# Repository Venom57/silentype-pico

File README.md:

# silentype-pico

USB controller for the **Apple Silentype** thermal printer (1980, Trendcom 200 mechanism),
built on a Raspberry Pi Pico 2, with a host-side PAPPL printer application that presents it
to macOS and Linux as an IPP Everywhere printer (no driver install). The printer itself is not
modified: the carrier board plugs into its original DE-9 cable.

## Why this works

The Silentype has no processor. Apple used the Trendcom mechanism without Trendcom's
controller, so the host does all the timing; on the Apple II that host was the interface
card's 2 KB ROM running on the 6502. Inside the printer there is only a 74LS673 16-bit shift
register with an output latch, three ULN2003 driver arrays (7-dot head, carriage stepper,
paper stepper), a 555 head-on watchdog and a margin switch. Anything that produces the right
16-bit words at the right times can drive it. The Pico replaces the card and the 6502.

## Architecture

The host turns pages into 7-dot bands; the Pico turns bands into exactly timed 16-bit words; the
carrier converts levels and fails safe; the printer, unchanged, latches and drives. Details in the
[design overview](docs/design-overview.md).

## Documentation

| Document | What it covers |
|---|---|
| [Design overview](docs/design-overview.md) | Architecture, design principles, design-decision log, glossary |
| [Printer interface](docs/printer-interface.md) | Sources, printer electronics, DE-9 pinout, the 16-bit word, bus timing diagram, Apple's card decode, print timing tables, motion, corrections log |
| [Firmware design](docs/firmware-design.md) | Execution model, PIO transport, column schedule, motion, queue and errors, safety, configuration and SET_PARAM, tests, open issues |
| [Host software](docs/host-software.md) | USB transport, ACK flow control, PAPPL app, `send_band.py`, installation, open issues |
| [Band protocol](docs/protocol.md) | Wire format: frames, commands, payloads, example bytes |
| [Carrier board](hardware/pcb/README.md) | Build pipeline, circuit, schematic sheets, renders, layout rules |
| [Bill of materials](hardware/BOM.md) | Component choices; [`BOM.csv`](hardware/BOM.csv) generated from the board |
| [Bring-up and tests](docs/bring-up.md) | What is verified, bench procedure with pass criteria, milestone plan, measurement log |
| [Known issues](docs/KNOWN-ISSUES.md) | Audit trail and every open issue |
| [Hardware interface evidence](docs/firmware-archaeology/HARDWARE-INTERFACE.md) | Signal-by-signal evidence from Apple's schematics and ROM |
| [Firmware README](firmware/README.md) | Build, file map, pins |

## Gallery

| Bare PCB, front | Bare PCB, back (mirrored) |
|---|---|
|  |  |

| Printer bus schematic | Bus timing |
|---|---|
|  |  |

| Firmware execution model | Host ACK flow |
|---|---|
|  |  |

More: [power and input schematics](hardware/pcb/README.md#schematic), [assembled top view](docs/images/render-top.png).

## Repository map

| Path | Contents |
|---|---|
| `firmware/` | Pico SDK project: CMake, TinyUSB CDC, PIO transport, print engine |
| `firmware/test/` | Host-side test harness: runs the real engine and parser on a PC (`make -C firmware/test`) |
| `hardware/pcb/` | Carrier v1.0 generated from code: `build_carrier.py`, `Makefile`, KiCad board, Gerbers, renders |
| `hardware/BOM.csv`, `hardware/BOM.md` | Bill of materials and component notes for carrier v1.0 |
| `host/pappl-app/` | PAPPL printer application |
| `host/tools/send_band.py` | Bench tool (no CUPS needed) |
| `host/linux/`, `host/macos/` | udev rule, systemd unit, launchd agent |
| `docs/protocol.md` | Band protocol (host ⇄ Pico) |
| `docs/signals.md` | DE-9 signal map and bus waveform |
| `docs/*.md` | Design documents (see Documentation above); `docs/images/` holds renders and diagrams |
| `docs/bring-up.md` | Bench bring-up procedure, milestone test plan, measurement log |
| `docs/KNOWN-ISSUES.md` | Audit trail and open issues |
| `docs/firmware-archaeology/` | Apple /// driver, Apple II card ROM, schematics, `HARDWARE-INTERFACE.md` (the definitive interface) |
| `docs/reference/` | Silentype manual, TA27850 pinout, Trendcom manual |

## Quick start

```
# firmware (needs the Pico SDK and an ARM toolchain)
export PICO_SDK_PATH=~/pico-sdk
cmake -B build -S firmware && cmake --build build      # → build/silentype.uf2

# firmware tests on the PC (gcc only)
make -C firmware/test

# printer-app tests against a fake Pico (needs PAPPL headers)
make -C host/pappl-app test

# carrier PCB: regenerate, route, DRC, Gerbers, renders (KiCad 10, Java 25, Freerouting 2.5)
make -C hardware/pcb FREEROUTING_JAR=/path/to/freerouting-2.5.0.jar

# talk to the printer without CUPS
python3 host/tools/send_band.py status
```

The PCB fab package is `hardware/pcb/fab/silentype-carrier-gerbers.zip` (2 layers, 1.6 mm,
100 × 56 mm; standard JLCPCB/PCBWay rules).

## Status

| Area | State |
|---|---|
| Reverse engineering | Done: Apple /// driver, Apple II card ROM, printer and card schematics, DE-9 pinout |
| Firmware | Written; host-simulated tests pass; **not yet built with the real Pico SDK** |
| Carrier PCB v1.0 | Routed, DRC clean (0 errors, 0 unconnected), Gerbers exported; not yet ordered |
| PAPPL app | Builds against libpappl 1.4.12 with no warnings; fake-Pico test passes (`make -C host/pappl-app test`); a real PAPPL server added the printer and printed a PNG end to end to a fake Pico. Not yet tried from a desktop print dialog or with a real printer |
| Bench | Not started |

## Milestones

- [x] **M0a** Apple /// SOS driver found and disassembled
- [x] **M0b** Card ROM, both schematics and DE-9 pinout found; serial PIO transport written
- [ ] **M1** Bench characterisation: head element count and resistance, supply current
- [ ] **M2** Carrier built; margin switch readable; bus enable and store verified on the scope
- [ ] **M3** Carriage homes and sweeps under Pico control
- [ ] **M4** A single column burns cleanly at conservative timing
- [ ] **M5** Test-pattern band prints in both directions
- [ ] **M6** Band protocol end to end via `host/tools/send_band.py`
- [ ] **M7** PAPPL app prints PWG raster; visible in the macOS/Linux print dialog
- [ ] **M8** `lp -d silentype file.pdf` produces paper
- [ ] **M9** Reverse-pass registration tuned

Pass criteria for each are in `docs/bring-up.md`.

## Safety model (read before powering anything)

The print head is the one irreplaceable part. Three independent layers turn it off:

1. **Printer's 555 watchdog (inside the printer).** It watches the head driver outputs; if any
   element stays on for about 5–6 ms it clears the 74LS673's outputs, motors included.
2. **Carrier bus enable (hardware).** The 74AHCT541 drives the bus only while GP6 is high. When
   the Pico is in reset, unpowered, or the guard drops GP6, the buffer releases the bus and the
   carrier's pull-ups hold SC = XC = 1, which asynchronously clears every printer output.
3. **Software guard (firmware).** Every burn is capped at 3000 µs, and an alarm on core 0 drops
   GP6 if a burn overruns. This catches logic bugs; it is not a substitute for 1 and 2.

Plus: fused 12 V (2 A PTC, reverse-polarity crowbar), fused printer 5 V (0.5 A PTC), and a
current-limited bench supply for first power-up. The firmware defaults to intensity level 1,
well below Apple's default 5, until the head has been characterised.

## Ground truth

All timing and bit positions come from Apple's own code and schematics, archived in
`docs/firmware-archaeology/`: the Apple /// `.SILENTYPE` driver (7-element head, burn timing,
wave-drive stepping, bidirectional printing with 2-column thermal lookback), the Apple II card
ROM 341-0039-00 with Marc Ressl's disassembly (exact bit order, store sequence, 8-level burn
table), the printer schematic 050-0023-01, the card schematics 050-0024-00/-01 and Apple KB
TA27850. `HARDWARE-INTERFACE.md` is the definitive summary.

Still unknown until the bench: exact column count on paper, reverse-pass trim, head element
resistance, and which of Apple's two burn tables the head prefers.

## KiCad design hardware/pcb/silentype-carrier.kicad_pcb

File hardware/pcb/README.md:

# Carrier board v1.0

[README](../../README.md) · [Design overview](../../docs/design-overview.md) · [Printer interface](../../docs/printer-interface.md) · [Firmware design](../../docs/firmware-design.md) · [Host software](../../docs/host-software.md) · **Carrier board** · [Bring-up and tests](../../docs/bring-up.md)

100 × 56 mm, 2-layer, all through-hole. Routed, **DRC clean (0 errors, 0 unconnected)**,
Gerbers exported; not yet ordered. The whole board is generated from `build_carrier.py`.

| File | What it is |
|---|---|
| `build_carrier.py` | Parts, nets, placement, design rules, keepouts, silkscreen; `place`, `finish`, `bare` steps |
| `gen_resistor_models.py` | Writes `models/`: resistor models with the correct 4-band colour code, and Bourns MF-RHT PTC fuse models |
| `check_drc.py` | Fails the build on any DRC error or unconnected net |
| `Makefile` | The whole pipeline |
| `silentype-carrier.kicad_pcb` | The generated, routed board (open it in KiCad 10 to inspect) |
| `fab/` | Outputs: `silentype-carrier-gerbers.zip`, drill files and maps, placement CSV, DRC report, renders |

## Build

```
make FREEROUTING_JAR=/path/to/freerouting-2.5.0.jar     # default: ~/.local/share/freerouting/
```

Needs KiCad 10 (`kicad-cli` and its Python `pcbnew` module), Java 25 and the Freerouting 2.5
jar (the linux-arm64 native CLI crashes after its first pass). Steps:

1. `gen_resistor_models.py` writes the banded resistor models.
2. `build_carrier.py place` builds the board and exports a Specctra DSN (silkscreen outlines and
   the GND net are removed from the DSN: GND is poured, not routed).
3. Freerouting routes every other net.
4. `build_carrier.py finish` imports the routes, pours GND on both layers, lays out silkscreen.
5. KiCad DRC; `check_drc.py` stops the build on any error or unconnected net.
6. `fab`: Gerbers (F/B copper, mask, paste, silk, edge), Excellon PTH/NPTH, drill maps, zip.
7. `render`: assembled top, bottom and angled views, plus bare-board front and back.

`make models` fetches only the 3D models this board uses from KiCad's official library into
`~/.local/share/kicad/3dmodels` (no system install needed). Renders only; Gerbers never depend on
3D models.

## Circuit

| Block | Parts | Function |
|---|---|---|
| Printer connector | J1 DE-9 female | Apple KB TA27850 pinout: 2 +5 V, 3/7 GND, 4 SD, 5 MS, 6 +12 V, 8 XC, 9 SC |
| 12 V input | J2, F1 2 A PTC, D1 1N5822, C1 470 µF | Head and motor supply; D1 crowbars a reversed plug so F1 trips |
| 5 V | U3 R-78E5.0-1.0, C2, C3, F2 0.5 A PTC → +5V_PRN; D2 → VSYS | Printer logic, buffer, Pico |
| Bus buffer | U2 74AHCT541, R1–R3 47 Ω | SD/SC/XC from 3.3 V to 5 V TTL (channels A2/A3/A1; spare inputs grounded) |
| Fail-safe enable | Q1 2N3904, R7 10 k (OE̅ pull-up), R8 4.7 k, R9 47 k, R4/R5 4.7 k pull-ups, R6 10 k pull-down | GP6 high → U2 drives. GP6 low, Pico in reset or unpowered → bus released, SC = XC = 1, printer cleared |
| Margin switch | R10 1 k, R11 10 k to 3V3, D3 BAT85 | MS → GP5, clamped to 3.3 V |
| Interface | SW1 feed (GP22), LED1 error (GP26, R12), LED2 power (R13), J3 UART (GP0/GP1) | Bench use |
| Test points | TP1 SD, TP2 SC, TP3 XC, TP4 MS, TP5 +12 V, TP6 +5 V, TP7 GND | Scope access |

## Schematic

Drawn from the generator's net list; `build_carrier.py` is authoritative.

## Renders

| Bare PCB, front | Bare PCB, back (mirrored) |
|---|---|
|  |  |

Resistors carry their real 4-band codes (models from `gen_resistor_models.py`); F1 and F2 are
yellow PTC polyfuses, labelled "F1 PTC 2A" and "F2 PTC 0.5A" on the silkscreen; each electrolytic
has a bold "+" beside its positive pad; diodes are marked "K" at the cathode.

## Layout and rules

- Cables enter on the left edge (jack top, DE-9 below). The Pico 2 / 2 W sits on 8.5 mm sockets
  along the right edge, USB at the top edge; its antenna end reaches the bottom edge with a
  no-copper keepout on both layers.
- Tracks 0.3 mm / clearance 0.2 mm; +12 V 1.2 mm; +5 V and GND 0.6 mm; vias 0.7/0.35 mm. Minimum
  track 0.15 mm because the router necks to about 0.18 mm between header pins (fab minimum 0.127).
- GND poured on both layers; Pico GND pins connect solid (edge pins cannot fit two spokes).
- Silkscreen: reference designators inside axial bodies; "F1 PTC 2A" / "F2 PTC 0.5A" fuse labels; bold "+" beside each electrolytic's
  positive pad; "K" at diode cathodes; UART pin labels; board title on the back between the
  Pico's pin rows.

## Render notes

KiCad's library has no 3D models for the CUI PJ-102AH jack (KiCad's generic jack stands in) or
the Bourns MF-RHT PTC fuses (generated by `gen_resistor_models.py`: yellow epoxy body on two legs). KiCad 10.0.7 on aarch64 crashes loading most `CP_Radial`/`C_Radial` STEP
models; the D10 dual-pitch can loads, so it is used for C1 and, scaled, for C2/C3.

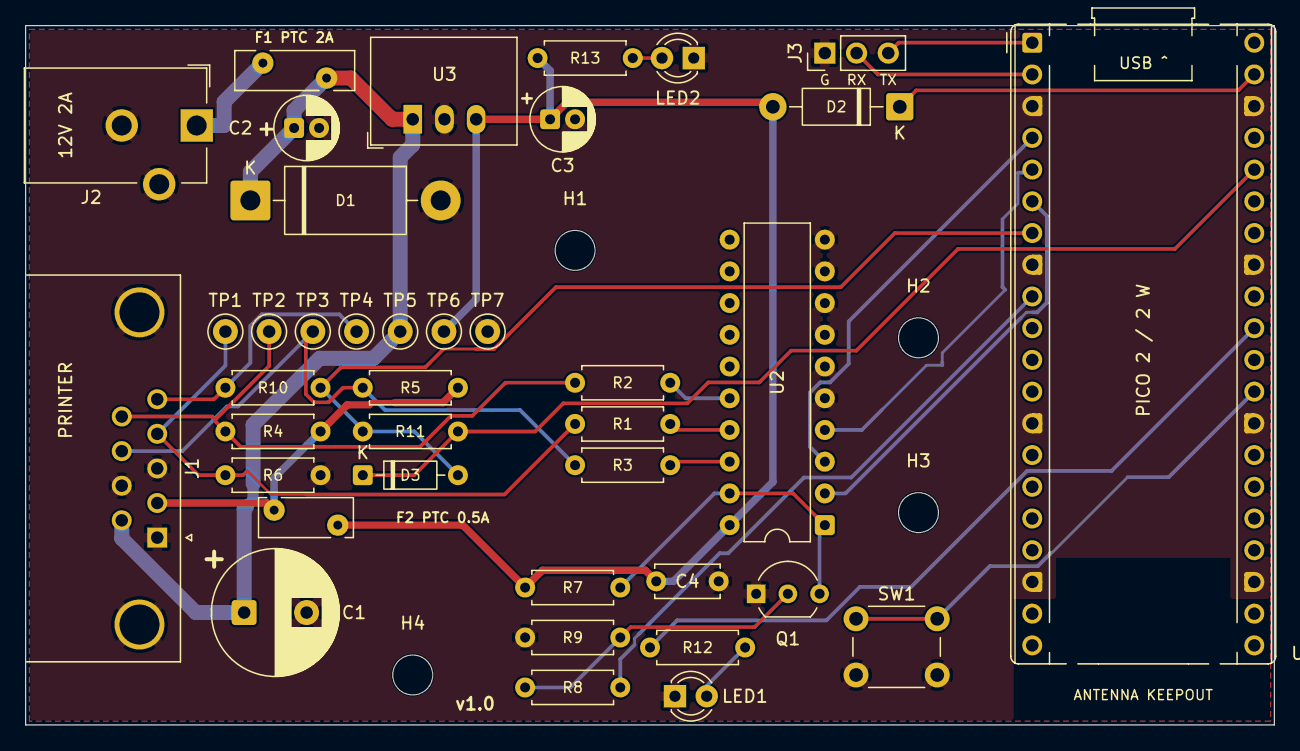
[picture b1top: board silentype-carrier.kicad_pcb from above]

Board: 2 copper layers, 100.0 x 56.0 mm, 43 parts (0 on the bottom side), 27 nets.

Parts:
C1: 470uF 25V; CP_Radial_D10.0mm_P5.00mm
C2: 10uF 25V; CP_Radial_D5.0mm_P2.00mm
C3: 22uF 10V; CP_Radial_D5.0mm_P2.00mm
C4: 100nF; C_Disc_D5.0mm_W2.5mm_P5.00mm
D1: 1N5822; D_DO-201AD_P15.24mm_Horizontal
D2: 1N5817; D_DO-41_SOD81_P10.16mm_Horizontal
D3: BAT85; D_DO-35_SOD27_P7.62mm_Horizontal
F1: PTC 2A; Fuse_Bourns_MF-RHT200
F2: PTC 0.5A; Fuse_Bourns_MF-RHT050
H1, H2, H3, H4: M3; MountingHole_3.2mm_M3
J1: DE-9 female (printer); DSUB-9_Socket_Horizontal_P2.77x2.84mm_EdgePinOffset7.70mm_H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
J2: 12V DC in; BarrelJack_CUI_PJ-102AH_Horizontal
J3: UART; PinHeader_1x03_P2.54mm_Vertical
LED1: ERR red; LED_D3.0mm
LED2: PWR green; LED_D3.0mm
Q1: 2N3904; TO-92_Inline_Wide
R1, R2, R3: 47R; R_Axial_DIN0207_L6.3mm_D2.5mm_P7.62mm_Horizontal
R4, R5, R8: 4k7; R_Axial_DIN0207_L6.3mm_D2.5mm_P7.62mm_Horizontal
R6, R7, R11: 10k; R_Axial_DIN0207_L6.3mm_D2.5mm_P7.62mm_Horizontal
R9: 47k; R_Axial_DIN0207_L6.3mm_D2.5mm_P7.62mm_Horizontal
R10, R13: 1k; R_Axial_DIN0207_L6.3mm_D2.5mm_P7.62mm_Horizontal
R12: 330R; R_Axial_DIN0207_L6.3mm_D2.5mm_P7.62mm_Horizontal
SW1: FEED; SW_PUSH_6mm
TP1: SD; TestPoint_Keystone_5000-5004_Miniature
TP2: SC; TestPoint_Keystone_5000-5004_Miniature
TP3: XC; TestPoint_Keystone_5000-5004_Miniature
TP4: MS; TestPoint_Keystone_5000-5004_Miniature
TP5: +12V; TestPoint_Keystone_5000-5004_Miniature
TP6: +5V; TestPoint_Keystone_5000-5004_Miniature
TP7: GND; TestPoint_Keystone_5000-5004_Miniature
U1: Pico 2 / Pico 2 W; RaspberryPi_Pico_Common_THT
U2: 74AHCT541; DIP-20_W7.62mm
U3: R-78E5.0-1.0; Converter_DCDC_RECOM_R-78E-0.5_THT

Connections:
+3V3: D3.1, R11.2, U1.36
+5V: C3.1, C4.1, D2.2, F2.1, R7.1, R13.1, TP6.1, U2.20, U3.3
+5V_PRN: F2.2, J1.2, R4.2, R5.2
+12V: C1.1, C2.1, D1.1, F1.2, J1.6, TP5.1, U3.1
+12V_IN: F1.1, J2.1
BTN_FEED: SW1.1, U1.29
BUS_EN: R8.2, U1.9
GND: C1.2, C2.2, C3.2, C4.2, D1.2, J1.1, J1.3, J1.7, J1.SH, J2.2, J2.3, J3.1, LED1.1, LED2.1, Q1.1, R6.2, R9.1, SW1.2, TP7.1, U1.3, U1.8, U1.13, U1.18, U1.23, U1.28, U1.33, U1.38, U2.5, U2.6, U2.7, U2.8, U2.9, U2.10, U3.2
LED_ERR: R12.1, U1.31
LED_ERR_A: LED1.2, R12.2
LED_PWR: LED2.2, R13.2
MS_5V: J1.5, R10.1, TP4.1
MS_IN: D3.2, R10.2, R11.1, U1.7
OE_N: Q1.3, R7.2, U2.1, U2.19
Q1_B: Q1.2, R8.1, R9.2
SC_3V: U1.5, U2.4
SC_5V: J1.9, R2.1, R4.1, TP2.1
SC_B: R2.2, U2.16
SD_3V: U1.4, U2.3
SD_5V: J1.4, R1.1, R6.1, TP1.1
SD_B: R1.2, U2.17
UART_RX: J3.2, U1.2
UART_TX: J3.3, U1.1
VSYS: D2.1, U1.39
XC_3V: U1.6, U2.2
XC_5V: J1.8, R3.1, R5.1, TP3.1
XC_B: R3.2, U2.18

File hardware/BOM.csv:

Refs,Qty,Value,Part,Footprint
C1,1,470uF 25V,electrolytic 470uF/25V low-ESR,Capacitor_THT:CP_Radial_D10.0mm_P5.00mm
C2,1,10uF 25V,electrolytic 10uF/25V,Capacitor_THT:CP_Radial_D5.0mm_P2.00mm
C3,1,22uF 10V,electrolytic 22uF/10V,Capacitor_THT:CP_Radial_D5.0mm_P2.00mm
C4,1,100nF,ceramic 100nF,Capacitor_THT:C_Disc_D5.0mm_W2.5mm_P5.00mm
D1,1,1N5822,1N5822 (reverse-polarity crowbar),Diode_THT:D_DO-201AD_P15.24mm_Horizontal
D2,1,1N5817,1N5817 (5V -> Pico VSYS),Diode_THT:D_DO-41_SOD81_P10.16mm_Horizontal
D3,1,BAT85,BAT85 (clamp MS_IN to 3V3),Diode_THT:D_DO-35_SOD27_P7.62mm_Horizontal
F1,1,PTC 2A,Bourns MF-RHT200,Fuse:Fuse_Bourns_MF-RHT200
F2,1,PTC 0.5A,Bourns MF-RHT050,Fuse:Fuse_Bourns_MF-RHT050
H1 H2 H3 H4,4,M3,M3 standoff,MountingHole:MountingHole_3.2mm_M3
J1,1,DE-9 female (printer),"DE-9 socket (female), right-angle PCB, 2.77 x 2.84 mm pitch, 9.12 mm hole-to-edge",Connector_Dsub:DSUB-9_Socket_Horizontal_P2.77x2.84mm_EdgePinOffset7.70mm_Housed_MountingHolesOffset9.12mm
J2,1,12V DC in,CUI PJ-102AH,Connector_BarrelJack:BarrelJack_CUI_PJ-102AH_Horizontal
J3,1,UART,1x3 2.54 mm header,Connector_PinHeader_2.54mm:PinHeader_1x03_P2.54mm_Vertical
LED1,1,ERR red,3 mm red LED,LED_THT:LED_D3.0mm
LED2,1,PWR green,3 mm green LED,LED_THT:LED_D3.0mm
Q1,1,2N3904,2N3904 (E-B-C),Package_TO_SOT_THT:TO-92_Inline_Wide
R1 R2 R3,3,47R,47R 1/4W,Resistor_THT:R_Axial_DIN0207_L6.3mm_D2.5mm_P7.62mm_Horizontal
R4 R5 R8,3,4k7,4.7k 1/4W,Resistor_THT:R_Axial_DIN0207_L6.3mm_D2.5mm_P7.62mm_Horizontal
R6 R7 R11,3,10k,10k 1/4W,Resistor_THT:R_Axial_DIN0207_L6.3mm_D2.5mm_P7.62mm_Horizontal
R9,1,47k,47k 1/4W,Resistor_THT:R_Axial_DIN0207_L6.3mm_D2.5mm_P7.62mm_Horizontal
R10 R13,2,1k,1k 1/4W,Resistor_THT:R_Axial_DIN0207_L6.3mm_D2.5mm_P7.62mm_Horizontal
R12,1,330R,330R 1/4W,Resistor_THT:R_Axial_DIN0207_L6.3mm_D2.5mm_P7.62mm_Horizontal
SW1,1,FEED,6x6 mm tactile,Button_Switch_THT:SW_PUSH_6mm
TP1,1,SD,Keystone 5000,TestPoint:TestPoint_Keystone_5000-5004_Miniature
TP2,1,SC,Keystone 5000,TestPoint:TestPoint_Keystone_5000-5004_Miniature
TP3,1,XC,Keystone 5000,TestPoint:TestPoint_Keystone_5000-5004_Miniature
TP4,1,MS,Keystone 5000,TestPoint:TestPoint_Keystone_5000-5004_Miniature
TP5,1,+12V,Keystone 5000,TestPoint:TestPoint_Keystone_5000-5004_Miniature
TP6,1,+5V,Keystone 5000,TestPoint:TestPoint_Keystone_5000-5004_Miniature
TP7,1,GND,Keystone 5001,TestPoint:TestPoint_Keystone_5000-5004_Miniature
U1,1,Pico 2 / Pico 2 W,"Raspberry Pi Pico 2 or Pico 2 W, on 2x 1x20 sockets",Module:RaspberryPi_Pico_Common_THT
U2,1,74AHCT541,SN74AHCT541N,Package_DIP:DIP-20_W7.62mm
U3,1,R-78E5.0-1.0,RECOM R-78E5.0-1.0,Converter_DCDC:Converter_DCDC_RECOM_R-78E-0.5_THT
,2,1x20 female header 2.54 mm,Pico sockets (U1),
,1,DIP-20 socket,for U2 (recommended),
,4,M3 standoff + screw,for H1-H4,
,1,12 V 2 A supply,"5.5 x 2.1 mm plug, centre positive",

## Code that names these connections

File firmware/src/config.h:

// config.h — silentype-pico. Single source of truth: pin map + mechanism timing.
// Every TBD_FROM_ROM is an INVENTED placeholder. They anchor to nothing. Replace
// each with a value extracted from the C800 ROM / SOS driver disassembly or a
// bench measurement (docs/reverse-engineering.md) before the head rail is connected.
#pragma once
#include <stdint.h>
#define TBD_FROM_ROM(...) __VA_ARGS__   // grep-able marker; variadic so brace initializers pass through

// ---- Head geometry — CONFIRMED from Apple /// SOS driver font table (docs/firmware-archaeology) ----
#define HEAD_DOTS          7                 // glyph columns never exceed $7F
#if HEAD_DOTS > 8
#error "band protocol column byte assumes HEAD_DOTS <= 8"
#endif

// ---- Pin map — SERIAL interface to the printer's 74LS673 (see HARDWARE-INTERFACE.md) ----
// DB-9: 4=SD, 9=SC, 8=XC, 5=MS. The printer contains latch + ULN2003 drivers + 555 ceiling.
#define PIN_SD             2                 // serial data  → DB9-4 (via level shifter)
#define PIN_SC             3                 // shift clock  → DB9-9 (rising edge shifts)
#define PIN_XC             4                 // store clock  → DB9-8 (rising edge latches; MUST be PIN_SC+1: PIO side-set; SC=XC=1 clears)
#define PIN_MS             5                 // margin switch ← DB9-5 (active low; pull-up)
#define PIN_BUS_EN         6                 // carrier v1.0: high = 74AHCT541 drives the bus (via Q1). Low/reset/
                                             // unpowered = bus released; carrier pull-ups hold SC=XC=1 = latch CLEAR.
#define PIN_HOME_SENSE     PIN_MS
#define PIN_PAPER_SENSE    21                // unused — no paper sensor on this printer
#define PIN_BTN_FEED       22
#define PIN_LED_ERR        26
#define PIN_ISENSE         27                // unused — current never crosses the carrier
#define ADC_ISENSE_CH      1

// Legacy parallel-GPIO names kept so print_engine.c compiles until the PIO transport lands.
#define PIN_HEAD_FIRST     10
#define HEAD_MASK          (((1u << HEAD_DOTS) - 1u) << PIN_HEAD_FIRST)
#define PIN_CARR_FIRST     17
#define PIN_FEED_FIRST     21

// 74LS673 word layout: word bit N = output YN; bit 15 is shifted first (first-in lands at Y15)
#define SR_CARR_SHIFT      0                 // bits 0-3 carriage phases
#define SR_FEED_SHIFT      4                 // bits 4-7 paper phases
#define SR_RW_BIT          8                 // write 0
#define SR_HEAD_SHIFT      9                 // bits 9-15 head elements (Y09 bottom … Y15 top)

#define HOME_SENSE_ACTIVE_LOW  1                 // schematic 050-0023-01: margin switch to GND

// ---- Mechanism constants — values marked ROM: are from the SOS driver ($0A58/$0AC0 etc.) ----
static const uint8_t CARR_PHASE_TABLE[4] = {0x1, 0x8, 0x4, 0x2};   // ROM: one-hot wave drive, LSR ring
#define CARR_STEP_INTERVAL_US    4032                  // ROM: VIA T1 = $0FC0 when stepping without printing
#define CARR_RAMP_STEPS          TBD_FROM_ROM(0)       // ROM has no ramp; keep 0 unless the motor stalls
#define CARR_RAMP_START_US       TBD_FROM_ROM(6000)
#define CARR_HOME_TIMEOUT_MS     3000
#define FEED_STEPS_PER_BAND      7                     // contiguous graphics; text adds LINE_SPACING_STEPS
#define LINE_SPACING_STEPS       2                     // manual: default line increment (CF0E)
#define PAPER_STEPS_PER_INCH     40                    // manual p.21: form feed 40 steps ≈ 1 inch
#define MAX_COLS                 TBD_FROM_ROM(560)     // 80 chars × 7 cols (card ROM printerRowNum=80); ruler-check M1
#define FEED_MOTOR_FITTED        1                     // ROM: separate 4-phase ring in $34 ($0A7A/$0A8B)
static const uint8_t FEED_PHASE_TABLE[4] = {0x1, 0x8, 0x4, 0x2};   // ROM: same wave drive
#define FEED_STEP_INTERVAL_US    4032                  // ROM: one step + 2× T1 $0FC0 in $0AAE → ~8 ms/step effective
#define PAPER_SENSE_FITTED       0                     // schematic: no paper-out sensor exists
#define PAPER_SENSE_ACTIVE_LOW   1

// ---- Bidirectional printing ----
// Reverse-pass columns land offset from forward-pass columns because of
// mechanical backlash + burn-vs-step phase. ROM has a compensation value.
#define REVERSE_OFFSET_STEPS     TBD_FROM_ROM(0)      // ROM trims via a per-column -4 µs timing adder on reverse passes, not a step offset. Bench.
#define REHOME_EVERY_N_BANDS     TBD_FROM_ROM(0)      // 0 = only at start/RESET

// ---- Thermal history compensation ----
// The ROM's scheme: pre-heat pulse only for elements cold ≥2 columns (see PREHEAT_US).
// That is what print_engine.c implements. The accumulator model (HEAT_DECAY/HEAT_K) is
// retained as an optional extra, default off.
#define HEAT_DECAY               0
#define HEAT_K                   0

// Head burn — two independent Apple sources disagree on magnitude:
//   Apple /// SOS driver:   main 640 µs (+256 dark), pre-heat 512, off 2624
//   Apple II card ROM 341-0039-00, 8 levels (docs/firmware-archaeology/HARDWARE-INTERFACE.md §3):
//     lvl:      0    1    2    3    4    5*   6    7       (*default)
//     main:   549  823 1098 1372 1646 1921 2195 2744 µs
//     preheat 735  588  470  294  196   98   24    5 µs   (cold elements only)
//     off    1225 1078  960  784  686  588  514  495 µs
// Levels 0..7 below follow the Apple II card table. Level 1 ≈ the Apple /// value.
// START AT LEVEL 1 ON THE BENCH and go up. Printer's own 555 (~6 ms) is the last-resort ceiling.
#define MAX_INTENSITY 7
#define INTENSITY_LEVELS (MAX_INTENSITY + 1)
static const uint16_t BURN_US   [MAX_INTENSITY + 1] = { 549,  823, 1098, 1372, 1646, 1921, 2195, 2744 };
static const uint16_t PREHEAT_US_TAB[MAX_INTENSITY + 1] = { 735,  588,  470,  294,  196,   98,   24,    5 };
static const uint16_t OFF_US    [MAX_INTENSITY + 1] = {1225, 1078,  960,  784,  686,  588,  514,  495 };
#define DEFAULT_INTENSITY        1      // deliberately below Apple's default 5 until the head is characterized
#define BURN_HARD_LIMIT_US       3000   // software guard; above table max, below printer's 555 (~6 ms)
#define COLUMN_TAIL_US           0      // Apple II card has no separate tail; /// had 512

// Head current sense: NOT POSSIBLE on this printer (drivers are internal). Kept at 0 = disabled.
#define ISENSE_MIN_mA_PER_DOT    0
#define ISENSE_MAX_mA_PER_DOT    0
#define ISENSE_SHUNT_mOHM        100

#define PREHEAT_US               PREHEAT_US_TAB[DEFAULT_INTENSITY]   // engine will switch to per-level tables
#define INTER_COL_COOLDOWN_US    OFF_US[DEFAULT_INTENSITY]

#define BAND_QUEUE_DEPTH  8
